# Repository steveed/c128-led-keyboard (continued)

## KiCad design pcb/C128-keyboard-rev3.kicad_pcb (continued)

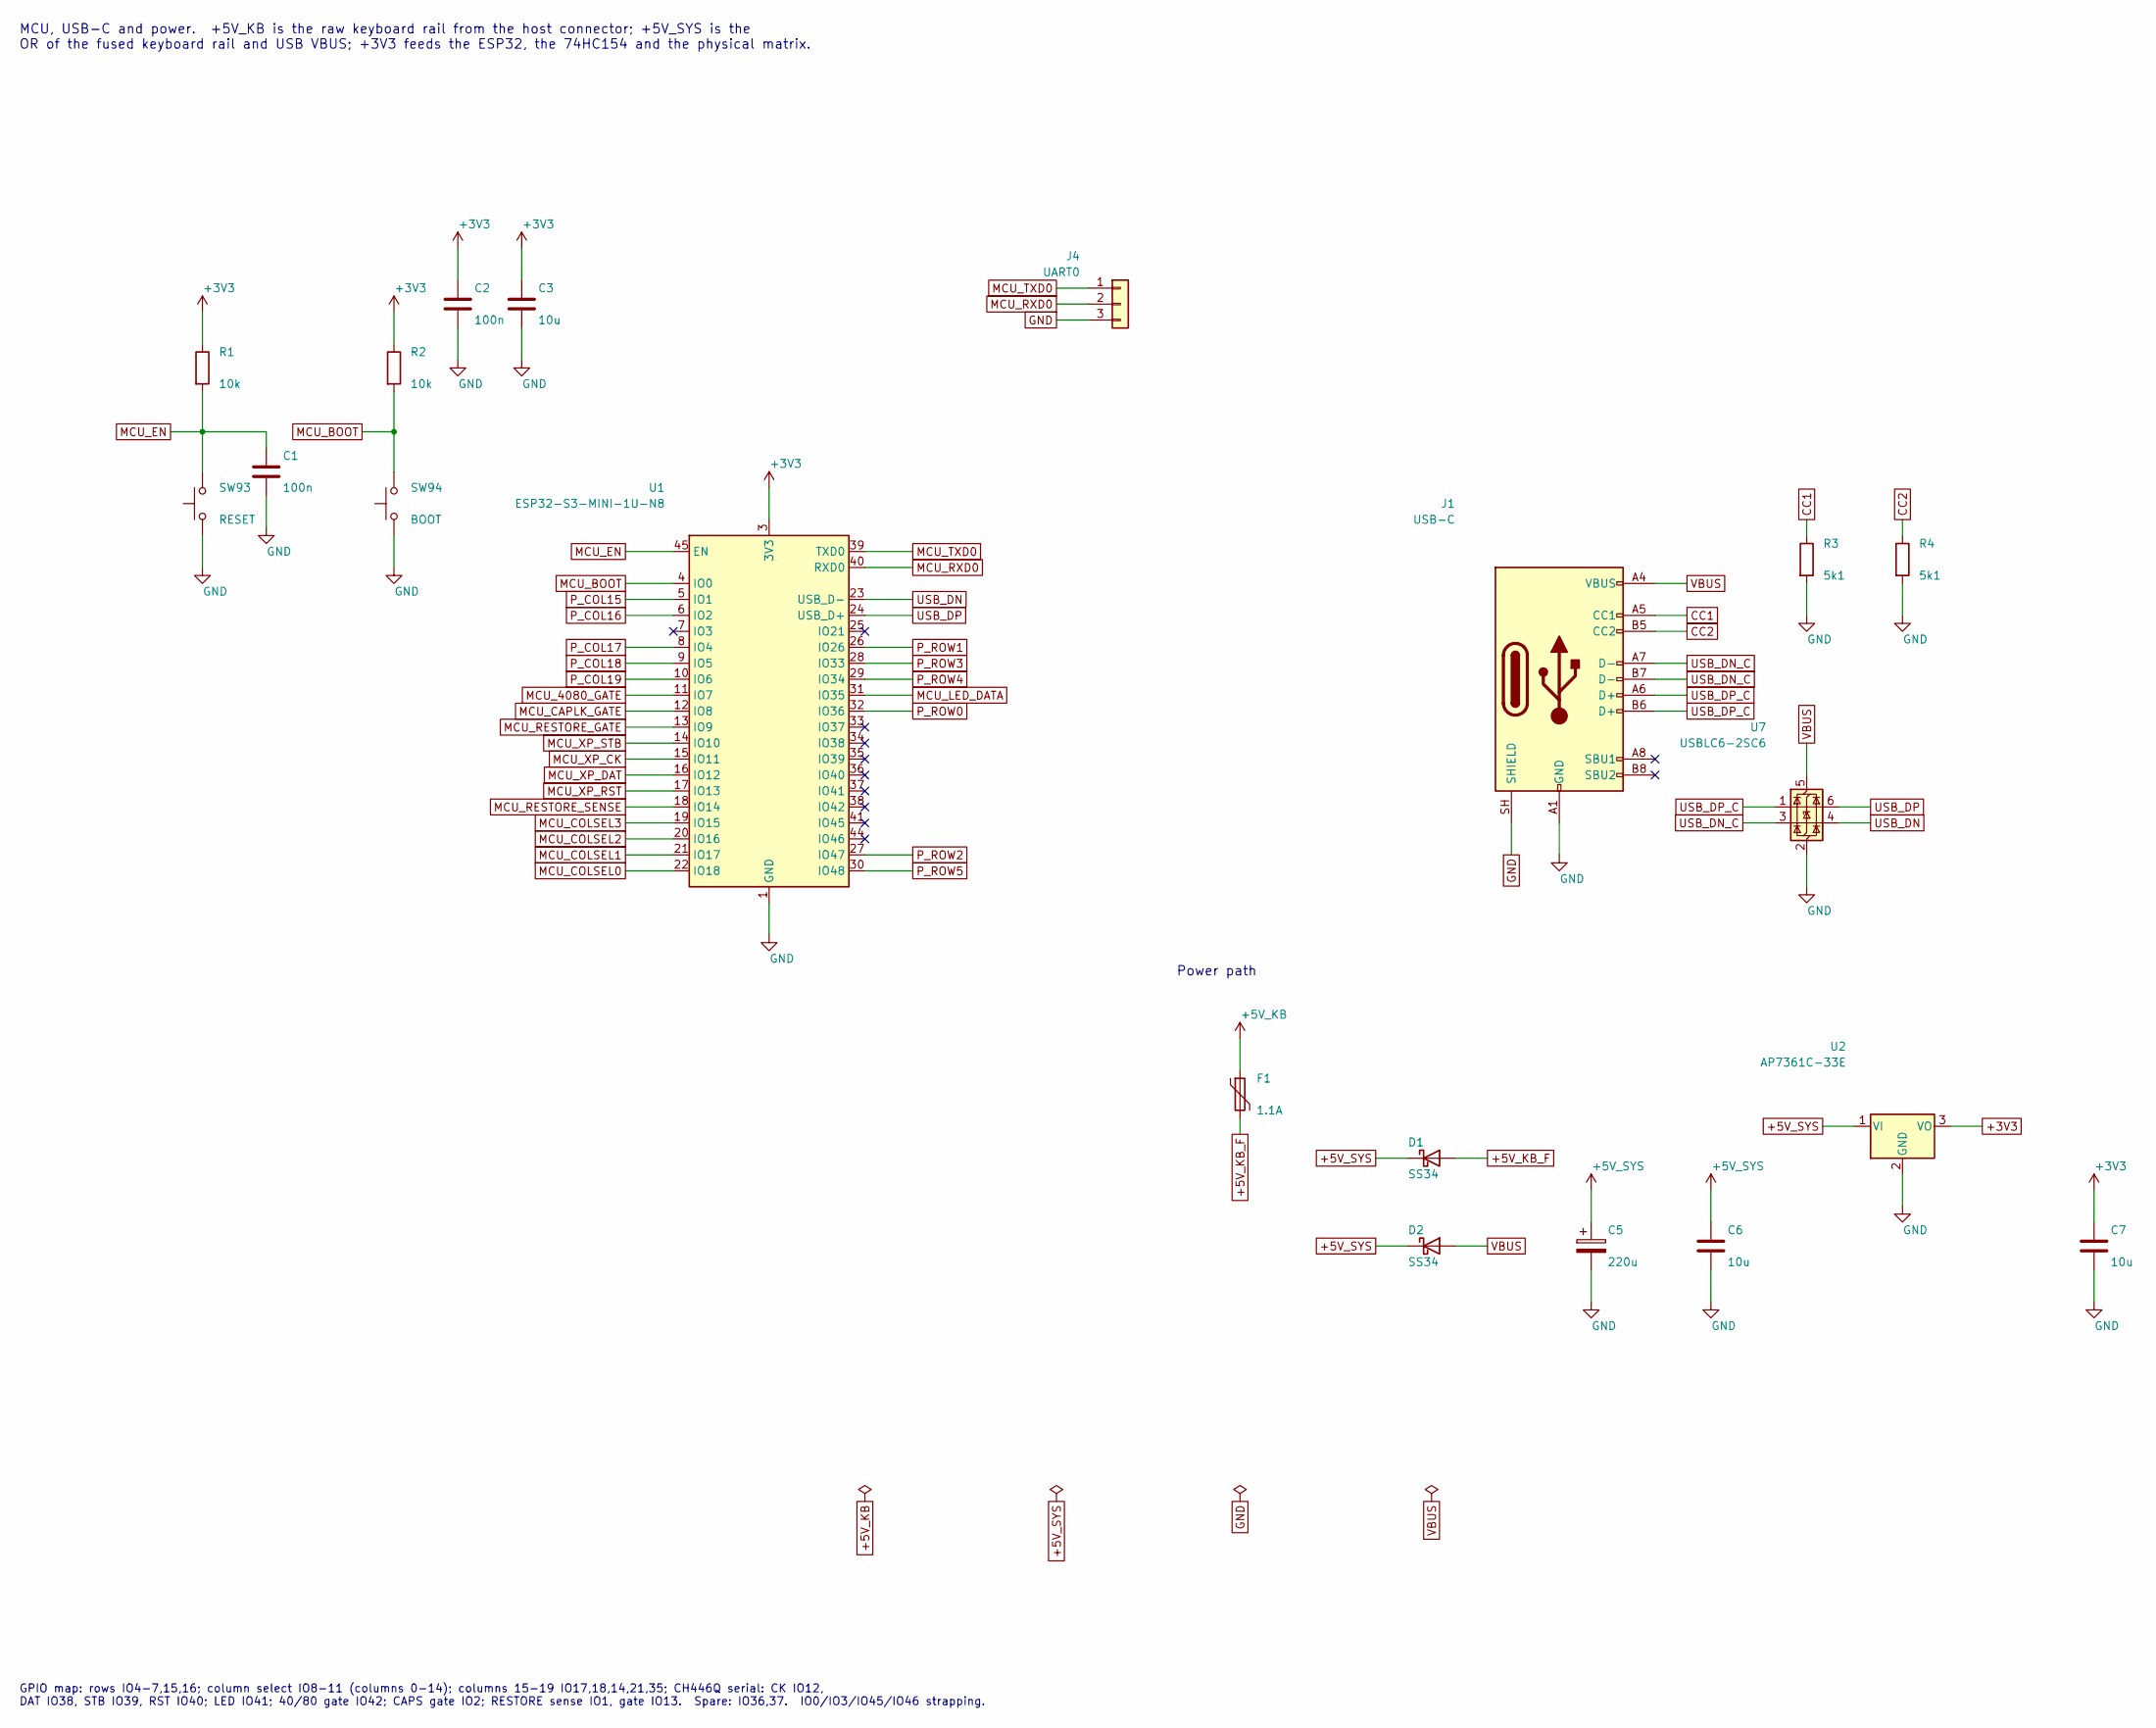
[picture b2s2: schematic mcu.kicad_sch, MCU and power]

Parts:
C1, C2: 100n; C_0603_1608Metric_Pad1.08x0.95mm_HandSolder; LCSC C14663
C3: 10u; C_0603_1608Metric_Pad1.08x0.95mm_HandSolder; LCSC C19702
C5: 220u; CP_Elec_6.3x7.7; LCSC C125979
C6, C7: 10u; C_1206_3216Metric_Pad1.33x1.80mm_HandSolder; LCSC C13585
D1, D2: SS34; D_SMA; LCSC C8678
F1: 1.1A; Fuse_1812_4532Metric; LCSC C142746
J1: USB-C; USB_C_Receptacle_ShouHan_TYPE-C-16P-3MD-040; LCSC C41417453
J4: UART0; PinHeader_1x03_P2.54mm_Vertical
R1, R2: 10k; R_0603_1608Metric_Pad0.98x0.95mm_HandSolder; LCSC C25804
R3, R4: 5k1; R_0603_1608Metric_Pad0.98x0.95mm_HandSolder; LCSC C23186
SW93: RESET; SW_SPST_PTS645Sx43SMTR92; LCSC C221880
SW94: BOOT; SW_SPST_PTS645Sx43SMTR92; LCSC C221880
U1: ESP32-S3-MINI-1U-N8; ESP32-S2-MINI-1U; LCSC C2980299
U2: AP7361C-33E; SOT-223-3_TabPin2; LCSC C500795
U7: USBLC6-2SC6; SOT-23-6; LCSC C7519

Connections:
+3V3: C2.1, C3.1, C7.1, R1.1, R2.1, U1.3 (3V3), U2.3 (VO); also elsewhere on the board
+5V_KB: F1.1; also elsewhere on the board
+5V_KB_F: D1.2 (A), F1.2
CC1: J1.A5 (CC1), R3.1
CC2: J1.B5 (CC2), R4.1
GND: C1.2, C2.2, C3.2, C5.2, C6.2, C7.2, J1.A1 (GND), J1.A12 (GND), J1.B1 (GND), J1.B12 (GND), J1.SH (SHIELD), J4.3, R3.2, R4.2, SW93.1, SW94.1, U1.1 (GND), U1.2 (GND), U1.42 (GND), U1.43 (GND), U1.46 (GND), U1.47 (GND), U1.48 (GND), U1.49 (GND), U1.50 (GND), U1.51 (GND), U1.52 (GND), U1.53 (GND), U1.54 (GND), U1.55 (GND), U1.56 (GND), U1.57 (GND), U1.58 (GND), U1.59 (GND), U1.60 (GND), U1.61 (GND), U1.62 (GND), U1.63 (GND), U1.64 (GND), U1.65 (GND), U2.2 (GND), U7.2 (GND); also elsewhere on the board
MCU_4080_GATE: U1.11 (IO7); also elsewhere on the board
MCU_BOOT: R2.2, SW94.2, U1.4 (IO0)
MCU_CAPLK_GATE: U1.12 (IO8); also elsewhere on the board
MCU_COLSEL0: U1.22 (IO18); also elsewhere on the board
MCU_COLSEL1: U1.21 (IO17); also elsewhere on the board
MCU_COLSEL2: U1.20 (IO16); also elsewhere on the board
MCU_COLSEL3: U1.19 (IO15); also elsewhere on the board
MCU_EN: C1.1, R1.2, SW93.2, U1.45 (EN)
MCU_LED_DATA: U1.31 (IO35); also elsewhere on the board
MCU_LED_EN: U1.34 (IO38); also elsewhere on the board
MCU_RESTORE_GATE: U1.13 (IO9); also elsewhere on the board
MCU_RESTORE_SENSE: U1.18 (IO14); also elsewhere on the board
MCU_RXD0: J4.2, U1.40 (RXD0)
MCU_TXD0: J4.1, U1.39 (TXD0)
MCU_XP_CK: U1.15 (IO11); also elsewhere on the board
MCU_XP_DAT: U1.16 (IO12); also elsewhere on the board
MCU_XP_RST: U1.17 (IO13); also elsewhere on the board
MCU_XP_STB: U1.14 (IO10); also elsewhere on the board
P_COL15: U1.5 (IO1); also elsewhere on the board
P_COL16: U1.6 (IO2); also elsewhere on the board
P_COL17: U1.8 (IO4); also elsewhere on the board
P_COL18: U1.9 (IO5); also elsewhere on the board
P_COL19: U1.10 (IO6); also elsewhere on the board
P_ROW0: U1.32 (IO36); also elsewhere on the board
P_ROW1: U1.26 (IO26); also elsewhere on the board
P_ROW2: U1.27 (IO47); also elsewhere on the board
P_ROW3: U1.28 (IO33); also elsewhere on the board
P_ROW4: U1.29 (IO34); also elsewhere on the board
P_ROW5: U1.30 (IO48); also elsewhere on the board
USB_DN: U1.23 (USB_D-), U7.4 (I/O2)
USB_DN_C: J1.A7 (D-), J1.B7 (D-), U7.3 (I/O2)
USB_DP: U1.24 (USB_D+), U7.6 (I/O1)
USB_DP_C: J1.A6 (D+), J1.B6 (D+), U7.1 (I/O1)
VBUS: D2.2 (A), J1.A4 (VBUS), J1.A9 (VBUS), J1.B4 (VBUS), J1.B9 (VBUS), U7.5 (VBUS)

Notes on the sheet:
GPIO map: rows IO4-7,15,16; column select IO8-11 (columns 0-14); columns 15-19 IO17,18,14,21,35; CH446Q serial: CK IO12, DAT IO38, STB IO39, RST IO40; LED IO41; 40/80 gate IO42; CAPS gate IO2; RESTORE sense IO1, gate IO13. Spare: IO36,37. IO0/IO3/IO45/IO46 strapping.
MCU, USB-C and power. +5V_KB is the raw keyboard rail from the host connector; +5V_SYS is the OR of the fused keyboard rail and USB VBUS; +3V3 feeds the ESP32, the 74HC154 and the physical matrix.
Power path

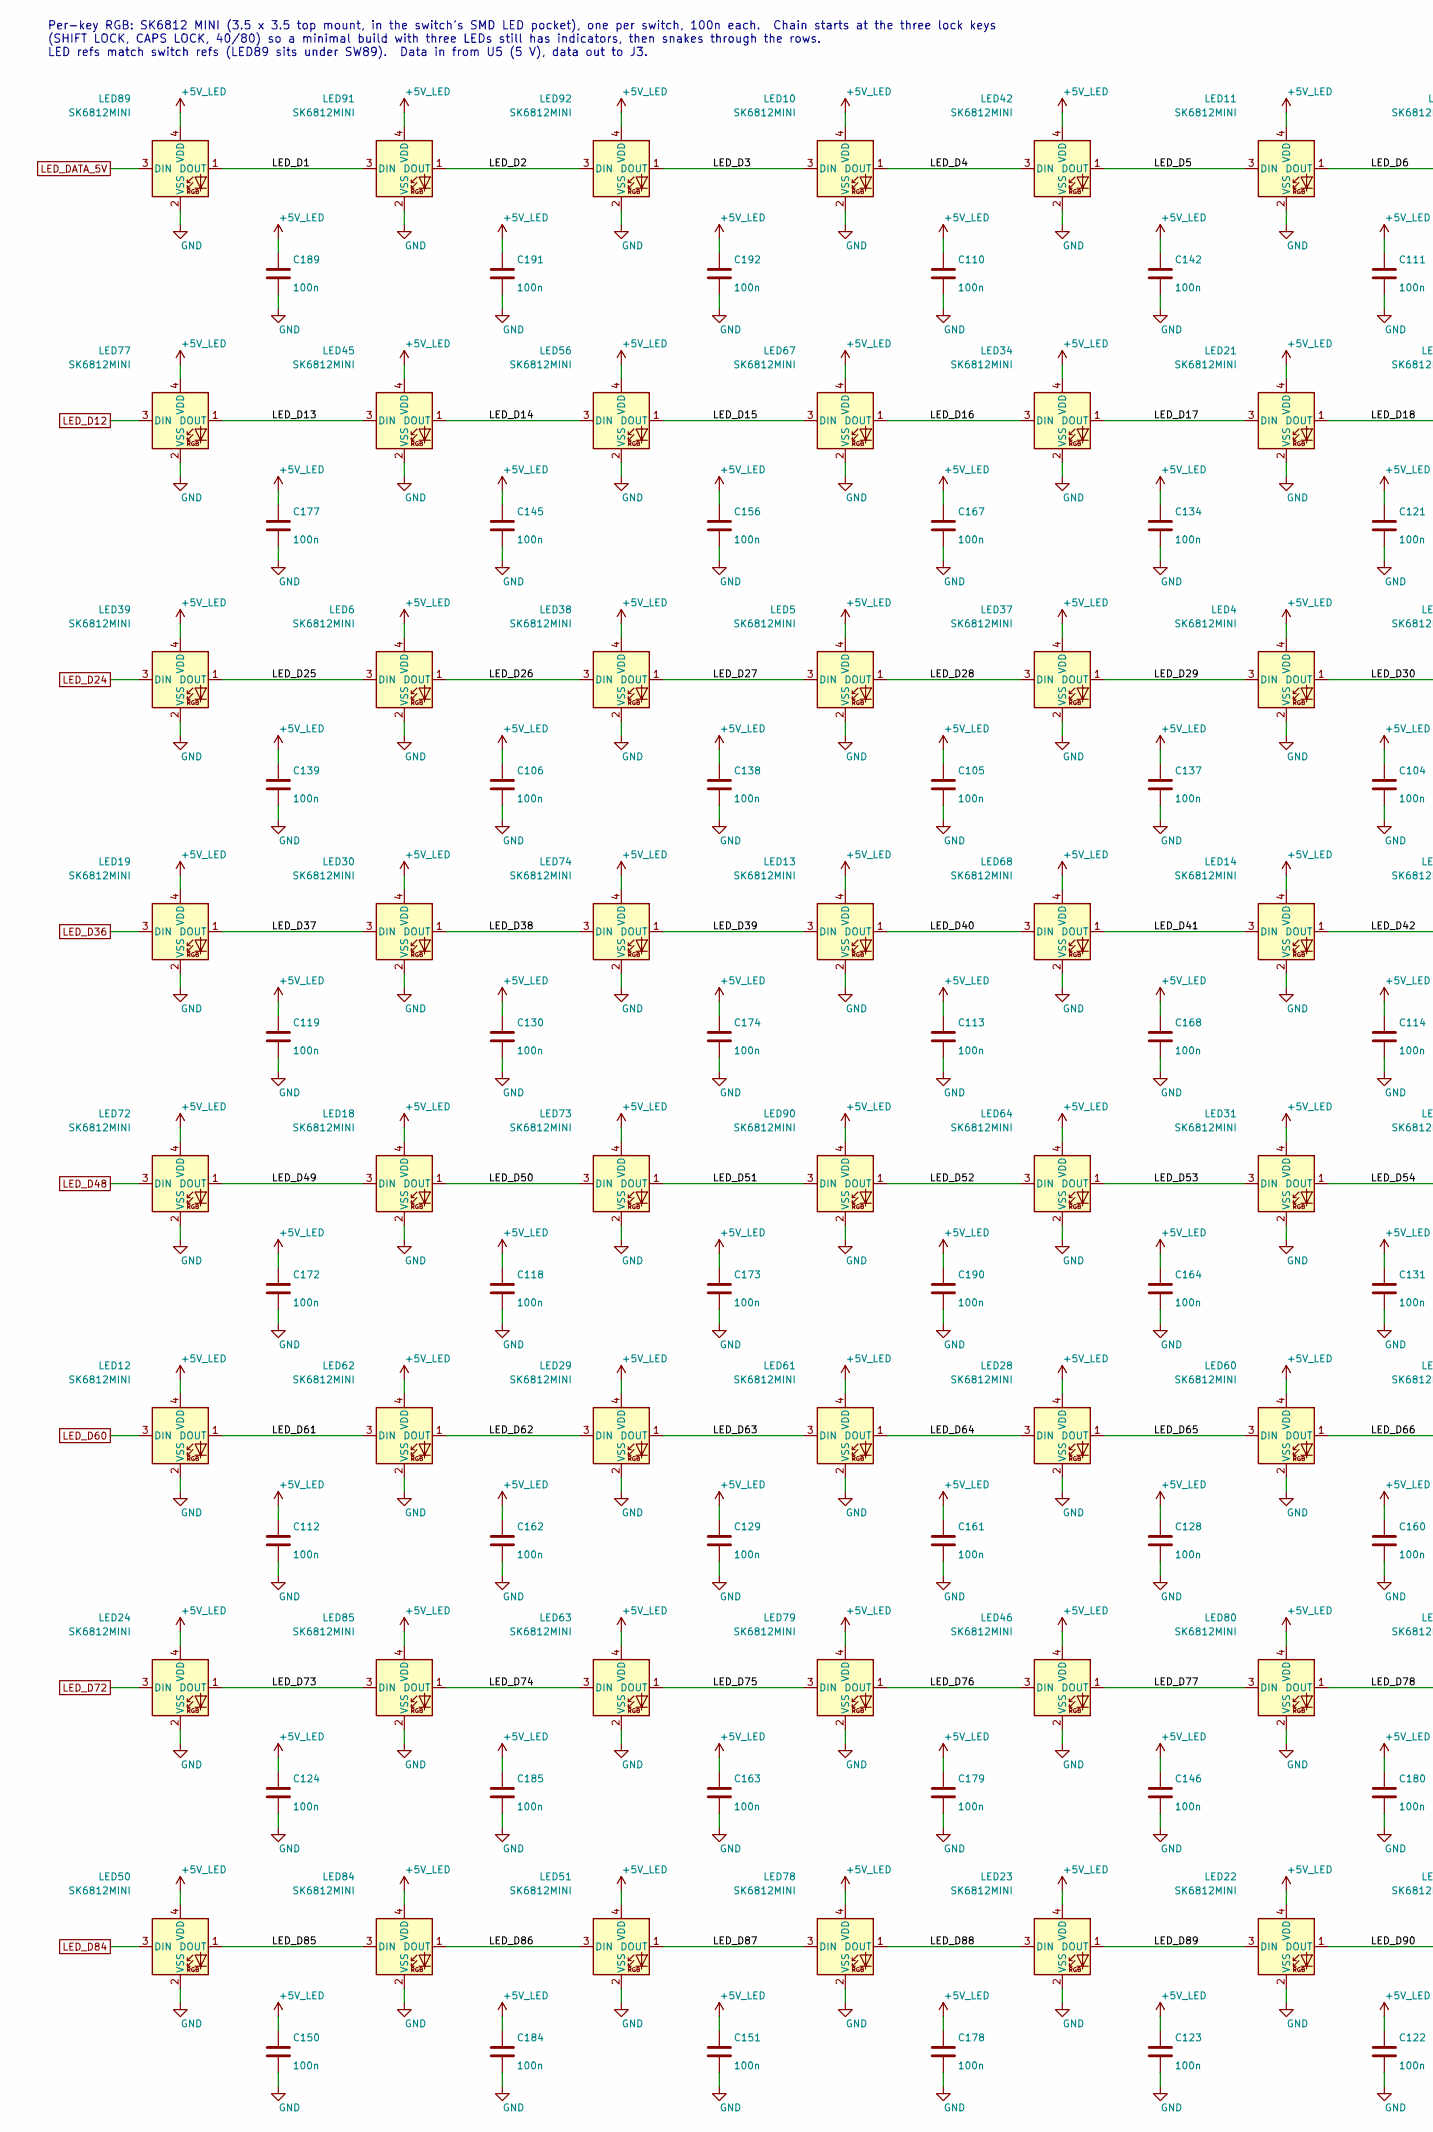
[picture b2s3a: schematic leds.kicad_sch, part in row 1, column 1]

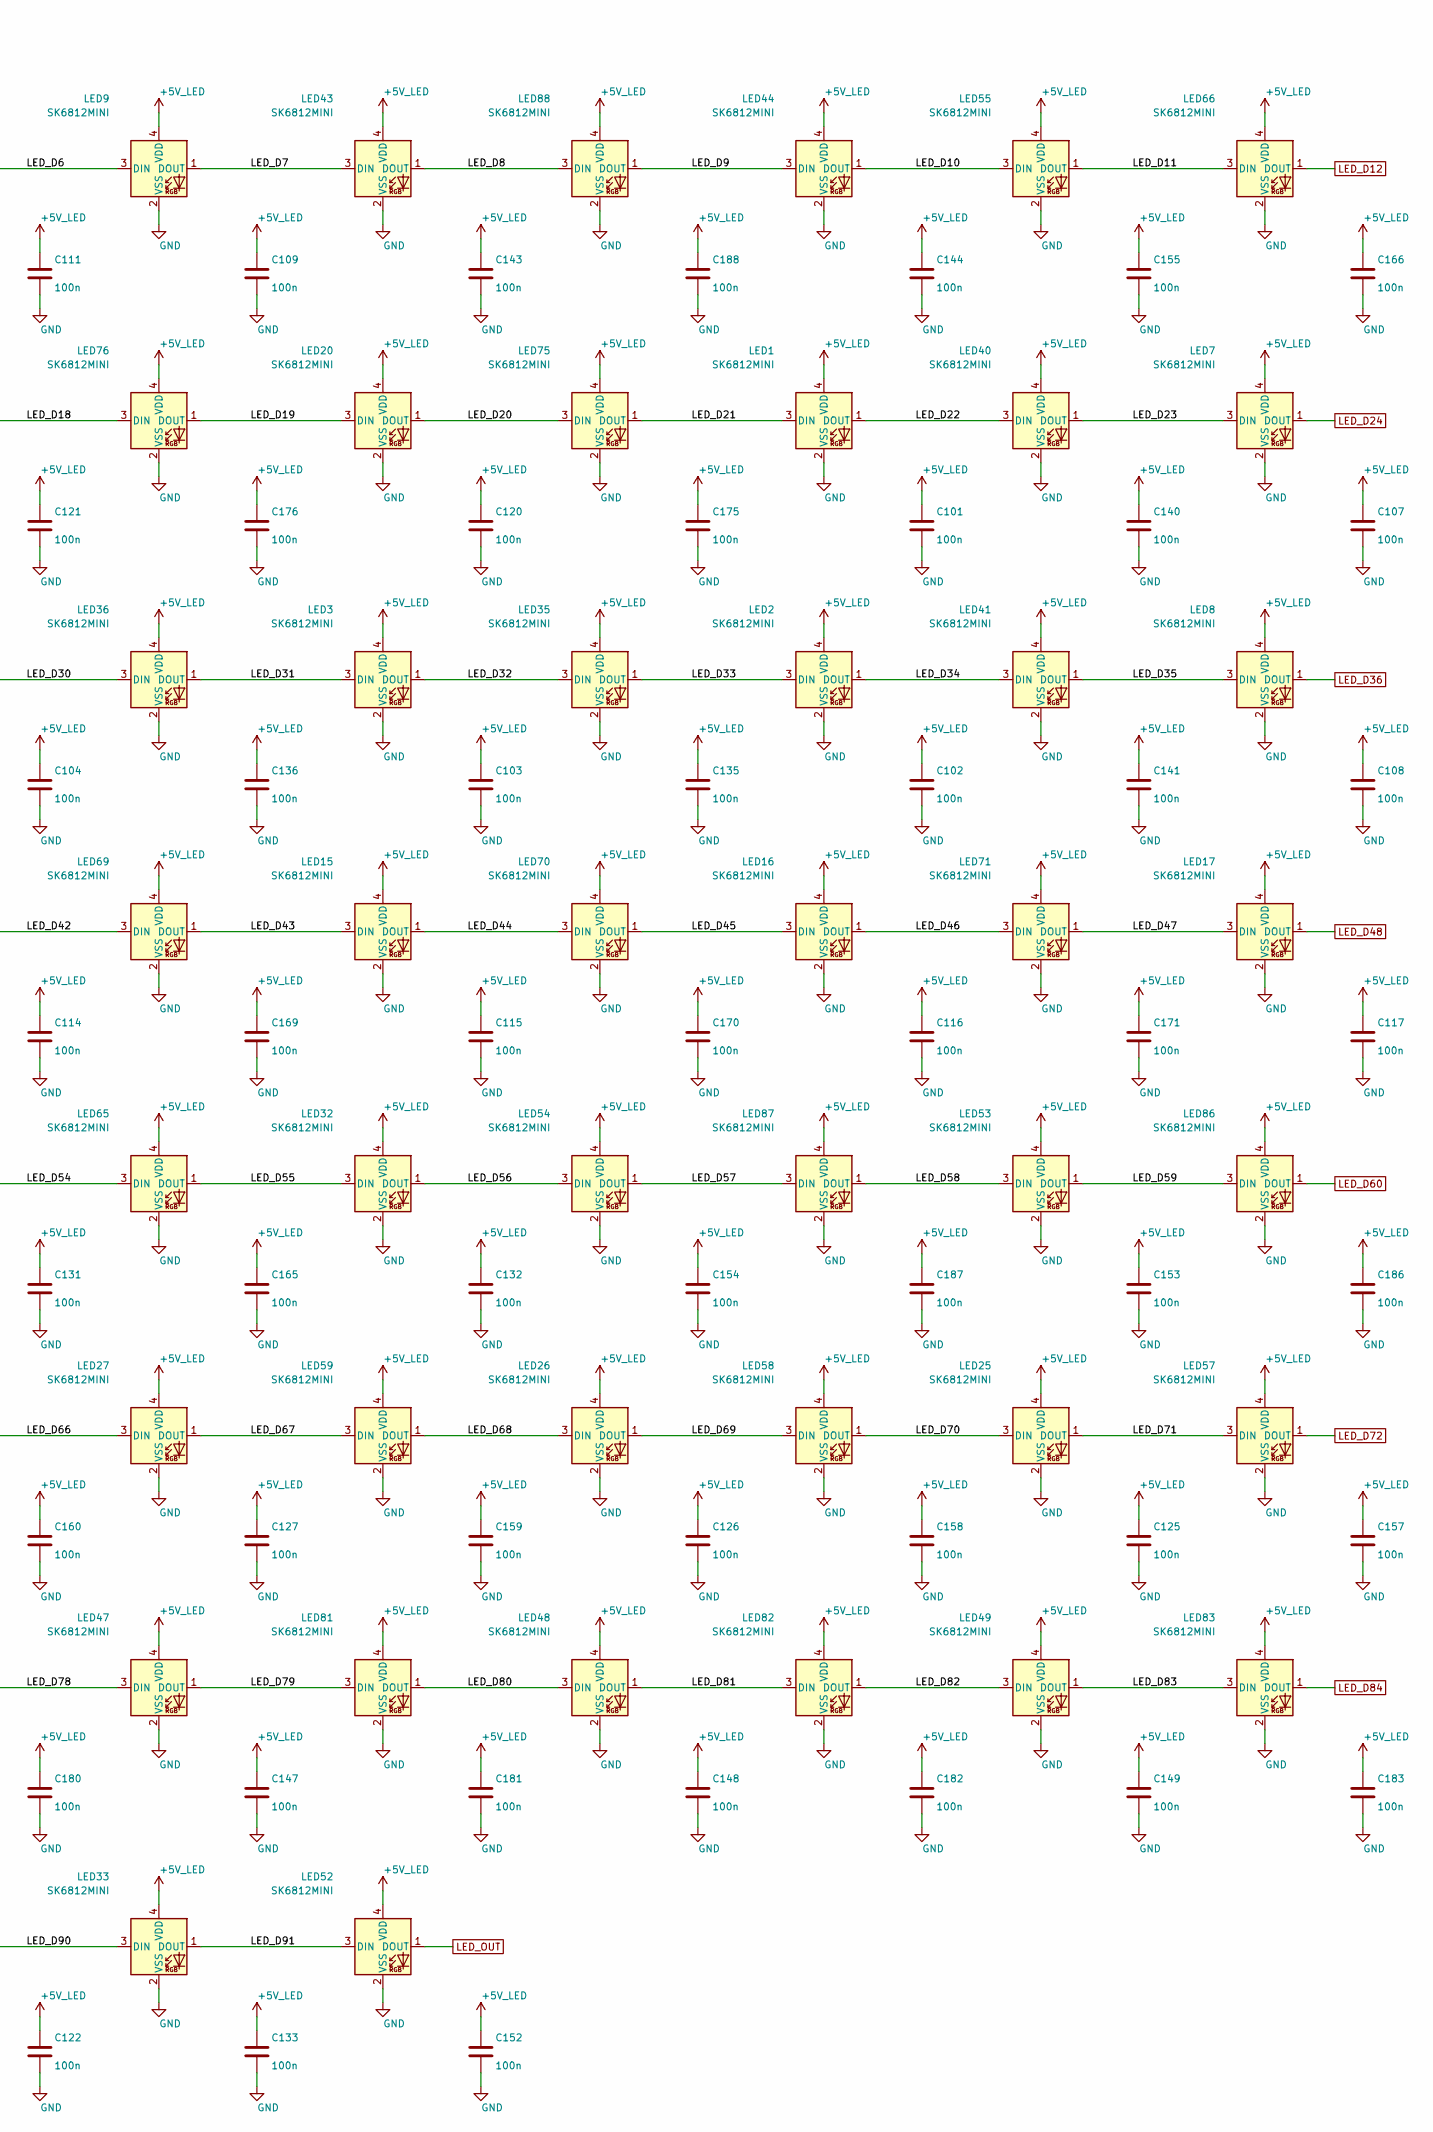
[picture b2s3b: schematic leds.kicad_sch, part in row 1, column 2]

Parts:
C101, C102, C103, C104, C105, C106, C107, C108, C109, C110, C111, C112, C113, C114, C115, C116, C117, C118, C119, C120, C121, C122, C123, C124, C125, C126, C127, C128, C129, C130, C131, C132, C133, C134, C135, C136, C137, C138, C139, C140, C141, C142, C143, C144, C145, C146, C147, C148, C149, C150, C151, C152, C153, C154, C155, C156, C157, C158, C159, C160, C161, C162, C163, C164, C165, C166, C167, C168, C169, C170, C171, C172, C173, C174, C175, C176, C177, C178, C179, C180, C181, C182, C183, C184, C185, C186, C187, C188, C189, C190, C191, C192: 100n; C_0603_1608Metric_Pad1.08x0.95mm_HandSolder; LCSC C14663
LED1, LED2, LED3, LED4, LED5, LED6, LED7, LED8, LED9, LED10, LED11, LED12, LED13, LED14, LED15, LED16, LED17, LED18, LED19, LED20, LED21, LED22, LED23, LED24, LED25, LED26, LED27, LED28, LED29, LED30, LED31, LED32, LED33, LED34, LED35, LED36, LED37, LED38, LED39, LED40, LED41, LED42, LED43, LED44, LED45, LED46, LED47, LED48, LED49, LED50, LED51, LED52, LED53, LED54, LED55, LED56, LED57, LED58, LED59, LED60, LED61, LED62, LED63, LED64, LED65, LED66, LED67, LED68, LED69, LED70, LED71, LED72, LED73, LED74, LED75, LED76, LED77, LED78, LED79, LED80, LED81, LED82, LED83, LED84, LED85, LED86, LED87, LED88, LED89, LED90, LED91, LED92: SK6812MINI; LED_SK6812MINI_MX; LCSC C2886570

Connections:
/LEDs/LED_D1: LED89.1 (DOUT), LED91.3 (DIN)
/LEDs/LED_D2: LED91.1 (DOUT), LED92.3 (DIN)
/LEDs/LED_D3: LED10.3 (DIN), LED92.1 (DOUT)
/LEDs/LED_D4: LED10.1 (DOUT), LED42.3 (DIN)
/LEDs/LED_D5: LED11.3 (DIN), LED42.1 (DOUT)
/LEDs/LED_D6: LED9.3 (DIN), LED11.1 (DOUT)
/LEDs/LED_D7: LED9.1 (DOUT), LED43.3 (DIN)
/LEDs/LED_D8: LED43.1 (DOUT), LED88.3 (DIN)
/LEDs/LED_D9: LED44.3 (DIN), LED88.1 (DOUT)
/LEDs/LED_D10: LED44.1 (DOUT), LED55.3 (DIN)
/LEDs/LED_D11: LED55.1 (DOUT), LED66.3 (DIN)
/LEDs/LED_D13: LED45.3 (DIN), LED77.1 (DOUT)
/LEDs/LED_D14: LED45.1 (DOUT), LED56.3 (DIN)
/LEDs/LED_D15: LED56.1 (DOUT), LED67.3 (DIN)
/LEDs/LED_D16: LED34.3 (DIN), LED67.1 (DOUT)
/LEDs/LED_D17: LED21.3 (DIN), LED34.1 (DOUT)
/LEDs/LED_D18: LED21.1 (DOUT), LED76.3 (DIN)
/LEDs/LED_D19: LED20.3 (DIN), LED76.1 (DOUT)
/LEDs/LED_D20: LED20.1 (DOUT), LED75.3 (DIN)
/LEDs/LED_D21: LED1.3 (DIN), LED75.1 (DOUT)
/LEDs/LED_D22: LED1.1 (DOUT), LED40.3 (DIN)
/LEDs/LED_D23: LED7.3 (DIN), LED40.1 (DOUT)
/LEDs/LED_D25: LED6.3 (DIN), LED39.1 (DOUT)
/LEDs/LED_D26: LED6.1 (DOUT), LED38.3 (DIN)
/LEDs/LED_D27: LED5.3 (DIN), LED38.1 (DOUT)
/LEDs/LED_D28: LED5.1 (DOUT), LED37.3 (DIN)
/LEDs/LED_D29: LED4.3 (DIN), LED37.1 (DOUT)
/LEDs/LED_D30: LED4.1 (DOUT), LED36.3 (DIN)
/LEDs/LED_D31: LED3.3 (DIN), LED36.1 (DOUT)
/LEDs/LED_D32: LED3.1 (DOUT), LED35.3 (DIN)
/LEDs/LED_D33: LED2.3 (DIN), LED35.1 (DOUT)
/LEDs/LED_D34: LED2.1 (DOUT), LED41.3 (DIN)
/LEDs/LED_D35: LED8.3 (DIN), LED41.1 (DOUT)
/LEDs/LED_D37: LED19.1 (DOUT), LED30.3 (DIN)
/LEDs/LED_D38: LED30.1 (DOUT), LED74.3 (DIN)
/LEDs/LED_D39: LED13.3 (DIN), LED74.1 (DOUT)
/LEDs/LED_D40: LED13.1 (DOUT), LED68.3 (DIN)
/LEDs/LED_D41: LED14.3 (DIN), LED68.1 (DOUT)
/LEDs/LED_D42: LED14.1 (DOUT), LED69.3 (DIN)
/LEDs/LED_D43: LED15.3 (DIN), LED69.1 (DOUT)
/LEDs/LED_D44: LED15.1 (DOUT), LED70.3 (DIN)
/LEDs/LED_D45: LED16.3 (DIN), LED70.1 (DOUT)
/LEDs/LED_D46: LED16.1 (DOUT), LED71.3 (DIN)
/LEDs/LED_D47: LED17.3 (DIN), LED71.1 (DOUT)
/LEDs/LED_D49: LED18.3 (DIN), LED72.1 (DOUT)
/LEDs/LED_D50: LED18.1 (DOUT), LED73.3 (DIN)
/LEDs/LED_D51: LED73.1 (DOUT), LED90.3 (DIN)
/LEDs/LED_D52: LED64.3 (DIN), LED90.1 (DOUT)
/LEDs/LED_D53: LED31.3 (DIN), LED64.1 (DOUT)
/LEDs/LED_D54: LED31.1 (DOUT), LED65.3 (DIN)
/LEDs/LED_D55: LED32.3 (DIN), LED65.1 (DOUT)
/LEDs/LED_D56: LED32.1 (DOUT), LED54.3 (DIN)
/LEDs/LED_D57: LED54.1 (DOUT), LED87.3 (DIN)
/LEDs/LED_D58: LED53.3 (DIN), LED87.1 (DOUT)
/LEDs/LED_D59: LED53.1 (DOUT), LED86.3 (DIN)
/LEDs/LED_D61: LED12.1 (DOUT), LED62.3 (DIN)
/LEDs/LED_D62: LED29.3 (DIN), LED62.1 (DOUT)
/LEDs/LED_D63: LED29.1 (DOUT), LED61.3 (DIN)
/LEDs/LED_D64: LED28.3 (DIN), LED61.1 (DOUT)
/LEDs/LED_D65: LED28.1 (DOUT), LED60.3 (DIN)
/LEDs/LED_D66: LED27.3 (DIN), LED60.1 (DOUT)
/LEDs/LED_D67: LED27.1 (DOUT), LED59.3 (DIN)
/LEDs/LED_D68: LED26.3 (DIN), LED59.1 (DOUT)
/LEDs/LED_D69: LED26.1 (DOUT), LED58.3 (DIN)
/LEDs/LED_D70: LED25.3 (DIN), LED58.1 (DOUT)
/LEDs/LED_D71: LED25.1 (DOUT), LED57.3 (DIN)
/LEDs/LED_D73: LED24.1 (DOUT), LED85.3 (DIN)
/LEDs/LED_D74: LED63.3 (DIN), LED85.1 (DOUT)
/LEDs/LED_D75: LED63.1 (DOUT), LED79.3 (DIN)
/LEDs/LED_D76: LED46.3 (DIN), LED79.1 (DOUT)
/LEDs/LED_D77: LED46.1 (DOUT), LED80.3 (DIN)
/LEDs/LED_D78: LED47.3 (DIN), LED80.1 (DOUT)
/LEDs/LED_D79: LED47.1 (DOUT), LED81.3 (DIN)
/LEDs/LED_D80: LED48.3 (DIN), LED81.1 (DOUT)
/LEDs/LED_D81: LED48.1 (DOUT), LED82.3 (DIN)
/LEDs/LED_D82: LED49.3 (DIN), LED82.1 (DOUT)
/LEDs/LED_D83: LED49.1 (DOUT), LED83.3 (DIN)
/LEDs/LED_D85: LED50.1 (DOUT), LED84.3 (DIN)
/LEDs/LED_D86: LED51.3 (DIN), LED84.1 (DOUT)
/LEDs/LED_D87: LED51.1 (DOUT), LED78.3 (DIN)
/LEDs/LED_D88: LED23.3 (DIN), LED78.1 (DOUT)
/LEDs/LED_D89: LED22.3 (DIN), LED23.1 (DOUT)
/LEDs/LED_D90: LED22.1 (DOUT), LED33.3 (DIN)
/LEDs/LED_D91: LED33.1 (DOUT), LED52.3 (DIN)
GND: C101.2, C102.2, C103.2, C104.2, C105.2, C106.2, C107.2, C108.2, C109.2, C110.2, C111.2, C112.2, C113.2, C114.2, C115.2, C116.2, C117.2, C118.2, C119.2, C120.2, C121.2, C122.2, C123.2, C124.2, C125.2, C126.2, C127.2, C128.2, C129.2, C130.2, C131.2, C132.2, C133.2, C134.2, C135.2, C136.2, C137.2, C138.2, C139.2, C140.2, C141.2, C142.2, C143.2, C144.2, C145.2, C146.2, C147.2, C148.2, C149.2, C150.2, C151.2, C152.2, C153.2, C154.2, C155.2, C156.2, C157.2, C158.2, C159.2, C160.2, C161.2, C162.2, C163.2, C164.2, C165.2, C166.2, C167.2, C168.2, C169.2, C170.2, C171.2, C172.2, C173.2, C174.2, C175.2, C176.2, C177.2, C178.2, C179.2, C180.2, C181.2, C182.2, C183.2, C184.2, C185.2, C186.2, C187.2, C188.2, C189.2, C190.2, C191.2, C192.2, LED1.2 (VSS), LED2.2 (VSS), LED3.2 (VSS), LED4.2 (VSS), LED5.2 (VSS), LED6.2 (VSS), LED7.2 (VSS), LED8.2 (VSS), LED9.2 (VSS), LED10.2 (VSS), LED11.2 (VSS), LED12.2 (VSS), LED13.2 (VSS), LED14.2 (VSS), LED15.2 (VSS), LED16.2 (VSS), LED17.2 (VSS), LED18.2 (VSS), LED19.2 (VSS), LED20.2 (VSS), LED21.2 (VSS), LED22.2 (VSS), LED23.2 (VSS), LED24.2 (VSS), LED25.2 (VSS), LED26.2 (VSS), LED27.2 (VSS), LED28.2 (VSS), LED29.2 (VSS), LED30.2 (VSS), LED31.2 (VSS), LED32.2 (VSS), LED33.2 (VSS), LED34.2 (VSS), LED35.2 (VSS), LED36.2 (VSS), LED37.2 (VSS), LED38.2 (VSS), LED39.2 (VSS), LED40.2 (VSS), LED41.2 (VSS), LED42.2 (VSS), LED43.2 (VSS), LED44.2 (VSS), LED45.2 (VSS), LED46.2 (VSS), LED47.2 (VSS), LED48.2 (VSS), LED49.2 (VSS), LED50.2 (VSS), LED51.2 (VSS), LED52.2 (VSS), LED53.2 (VSS), LED54.2 (VSS), LED55.2 (VSS), LED56.2 (VSS), LED57.2 (VSS), LED58.2 (VSS), LED59.2 (VSS), LED60.2 (VSS), LED61.2 (VSS), LED62.2 (VSS), LED63.2 (VSS), LED64.2 (VSS), LED65.2 (VSS), LED66.2 (VSS), LED67.2 (VSS), LED68.2 (VSS), LED69.2 (VSS), LED70.2 (VSS), LED71.2 (VSS), LED72.2 (VSS), LED73.2 (VSS), LED74.2 (VSS), LED75.2 (VSS), LED76.2 (VSS), LED77.2 (VSS), LED78.2 (VSS), LED79.2 (VSS), LED80.2 (VSS), LED81.2 (VSS), LED82.2 (VSS), LED83.2 (VSS), LED84.2 (VSS), LED85.2 (VSS), LED86.2 (VSS), LED87.2 (VSS), LED88.2 (VSS), LED89.2 (VSS), LED90.2 (VSS), LED91.2 (VSS), LED92.2 (VSS); also elsewhere on the board
LED_D12: LED66.1 (DOUT), LED77.3 (DIN)
LED_D24: LED7.1 (DOUT), LED39.3 (DIN)
LED_D36: LED8.1 (DOUT), LED19.3 (DIN)
LED_D48: LED17.1 (DOUT), LED72.3 (DIN)
LED_D60: LED12.3 (DIN), LED86.1 (DOUT)
LED_D72: LED24.3 (DIN), LED57.1 (DOUT)
LED_D84: LED50.3 (DIN), LED83.1 (DOUT)
LED_DATA_5V: LED89.3 (DIN); also elsewhere on the board
LED_OUT: LED52.1 (DOUT); also elsewhere on the board

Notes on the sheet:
Per-key RGB: SK6812 MINI (3.5 x 3.5 top mount, in the switch's SMD LED pocket), one per switch, 100n each. Chain starts at the three lock keys (SHIFT LOCK, CAPS LOCK, 40/80) so a minimal build with three LEDs still has indicators, then snakes through the rows. LED refs match switch refs (LED89 sits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

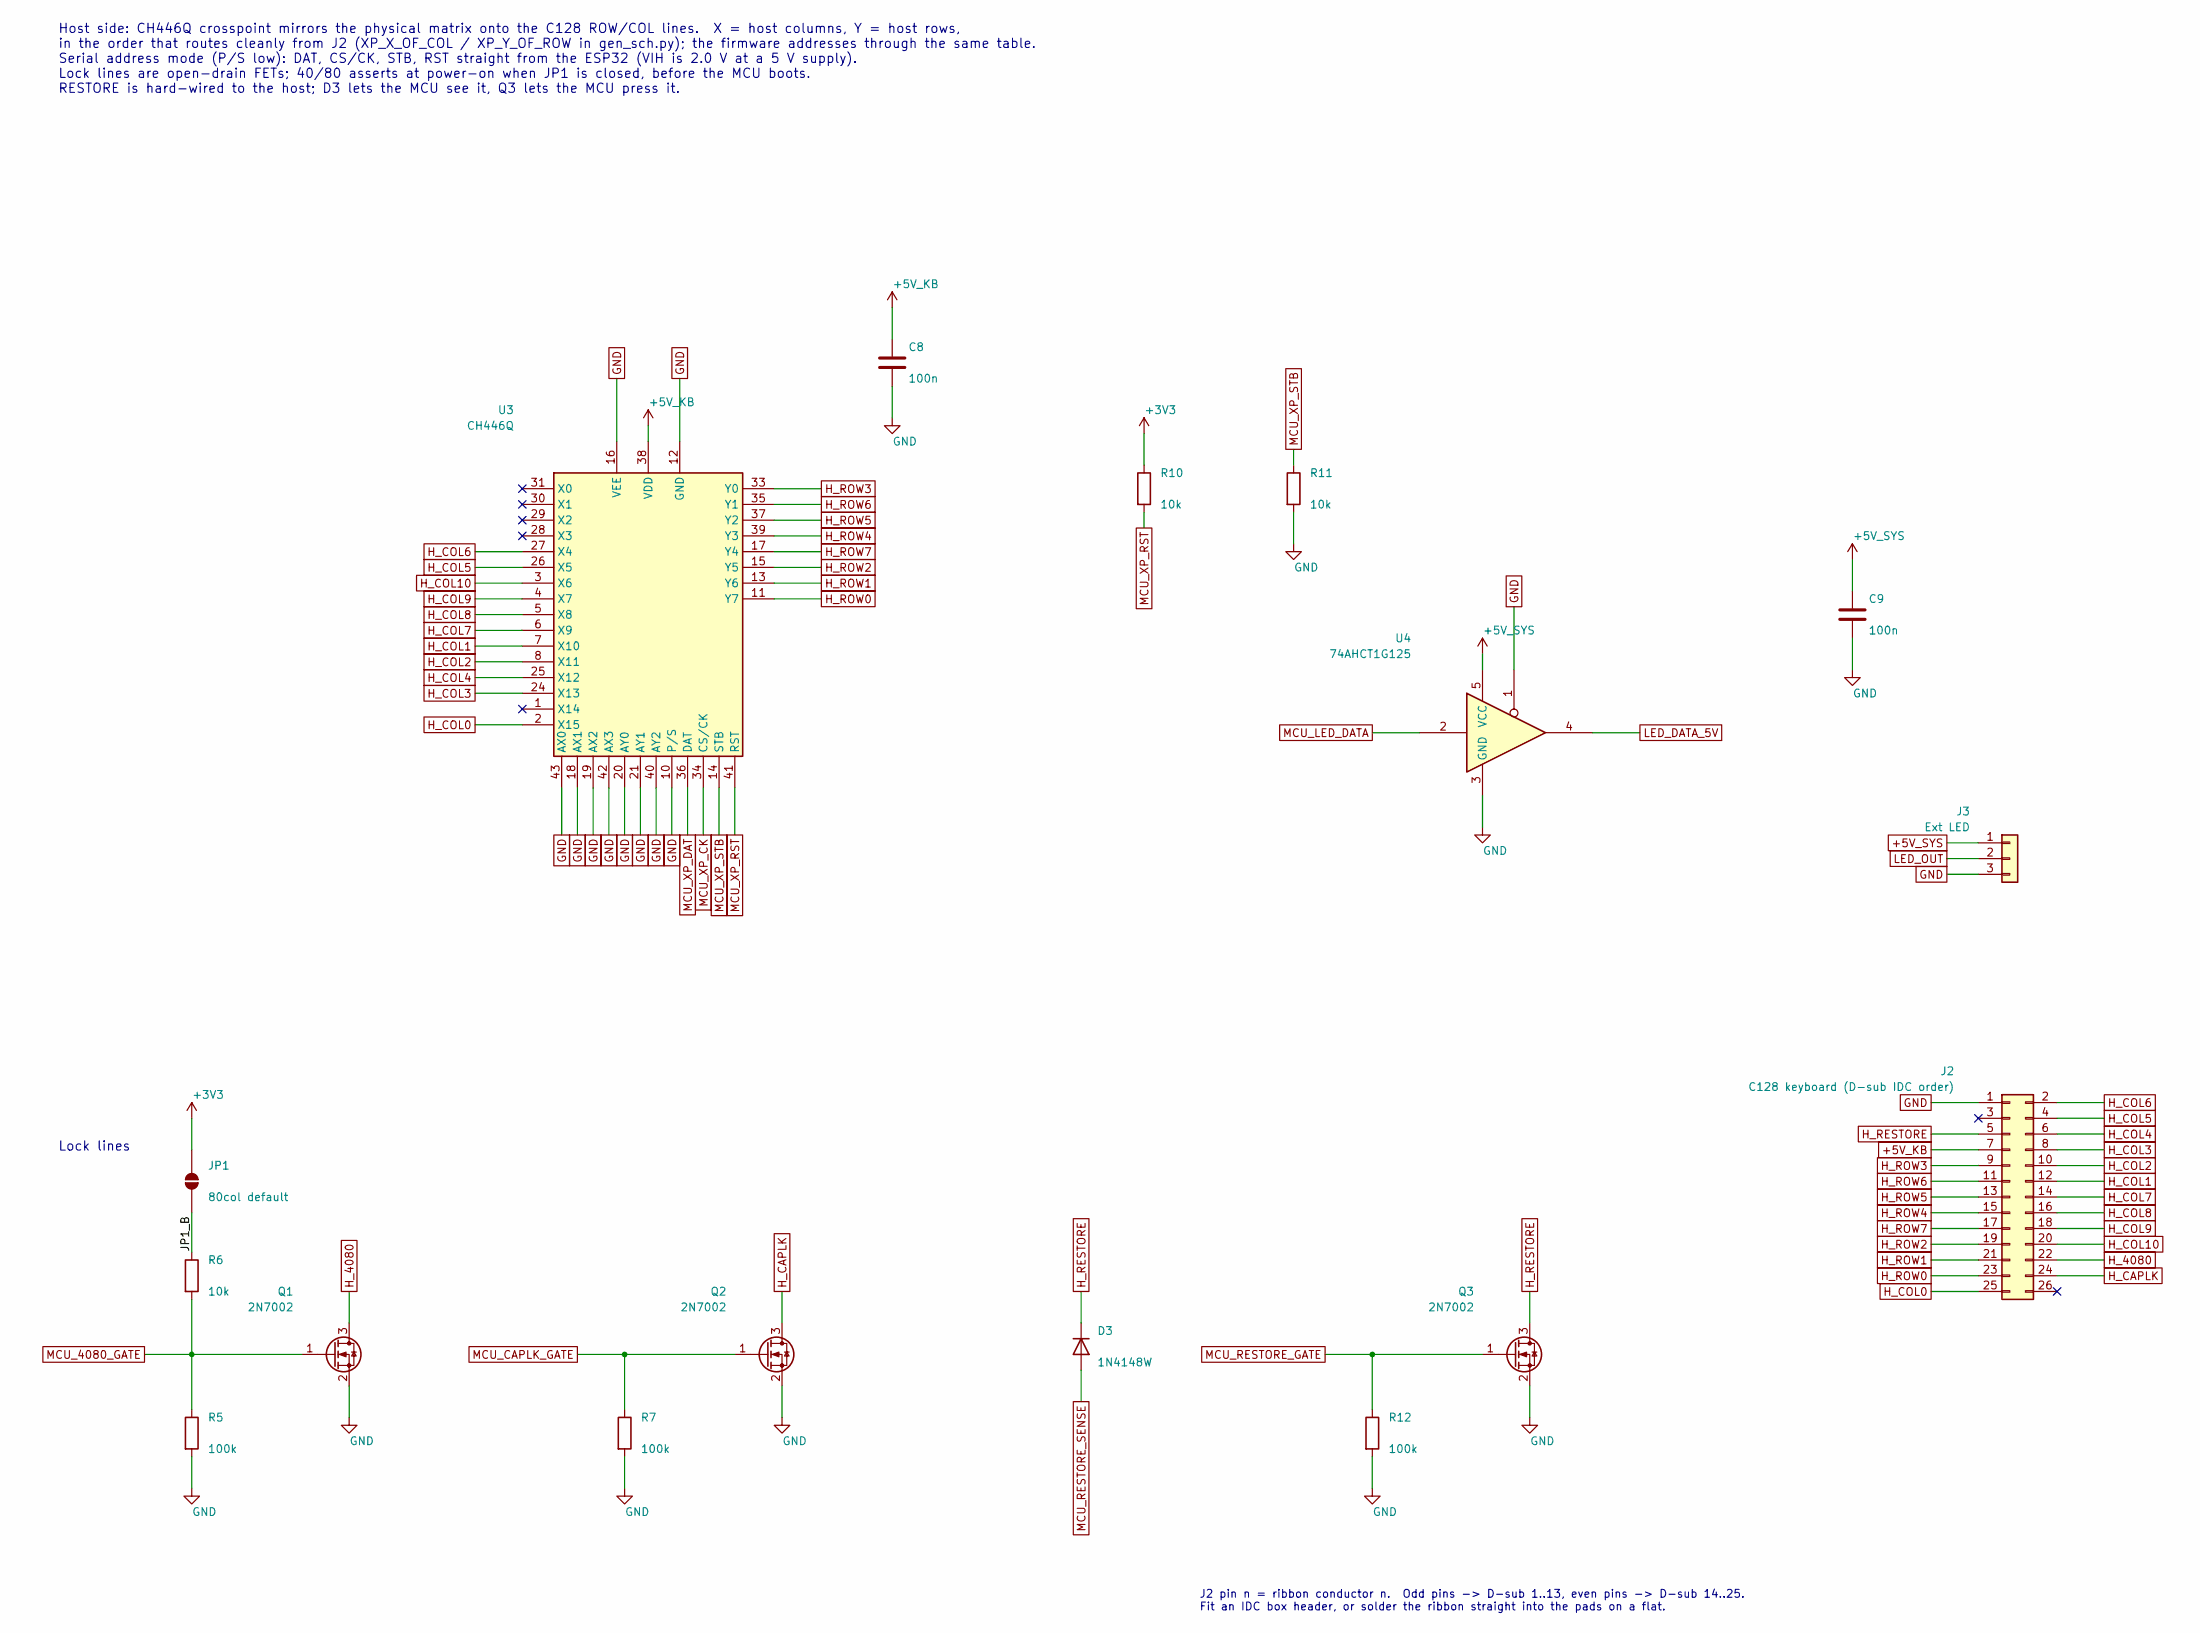
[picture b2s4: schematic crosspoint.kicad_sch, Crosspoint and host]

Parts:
C8, C9: 100n; C_0603_1608Metric_Pad1.08x0.95mm_HandSolder; LCSC C14663
D3: 1N4148W; D_SOD-123; LCSC C81598
J2: C128 keyboard (D-sub IDC order); IDC-Header_2x13_P2.54mm_Vertical
J3: Ext LED; PinHeader_1x03_P2.54mm_Vertical
JP1: 80col default; SolderJumper-2_P1.3mm_Open_RoundedPad1.0x1.5mm
Q1, Q2, Q3: 2N7002; SOT-23; LCSC C8545
R5, R7, R12: 100k; R_0603_1608Metric_Pad0.98x0.95mm_HandSolder; LCSC C25803
R6, R10, R11: 10k; R_0603_1608Metric_Pad0.98x0.95mm_HandSolder; LCSC C25804
U3: CH446Q; LQFP-44_10x10mm_P0.8mm; LCSC C109471
U4: 74AHCT1G125; SOT-23-5; LCSC C7484

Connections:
+3V3: JP1.2 (B), R10.1; also elsewhere on the board
+5V_KB: C8.1, J2.7, U3.38 (VDD); also elsewhere on the board
/Crosspoint and host/JP1_B: JP1.1 (A), R6.1
GND: C8.2, C9.2, J2.1, J3.3, Q1.2 (S), Q2.2 (S), Q3.2 (S), R5.2, R7.2, R11.2, R12.2, U3.10 (P/S), U3.12 (GND), U3.16 (VEE), U3.18 (AX1), U3.19 (AX2), U3.20 (AY0), U3.21 (AY1), U3.40 (AY2), U3.42 (AX3), U3.43 (AX0), U4.1, U4.3 (GND); also elsewhere on the board
H_4080: J2.22, Q1.3 (D)
H_CAPLK: J2.24, Q2.3 (D)
H_COL0: J2.25, U3.2 (X15)
H_COL1: J2.12, U3.7 (X10)
H_COL2: J2.10, U3.8 (X11)
H_COL3: J2.8, U3.24 (X13)
H_COL4: J2.6, U3.25 (X12)
H_COL5: J2.4, U3.26 (X5)
H_COL6: J2.2, U3.27 (X4)
H_COL7: J2.14, U3.6 (X9)
H_COL8: J2.16, U3.5 (X8)
H_COL9: J2.18, U3.4 (X7)
H_COL10: J2.20, U3.3 (X6)
H_RESTORE: D3.1 (K), J2.5, Q3.3 (D); also elsewhere on the board
H_ROW0: J2.23, U3.11 (Y7)
H_ROW1: J2.21, U3.13 (Y6)
H_ROW2: J2.19, U3.15 (Y5)
H_ROW3: J2.9, U3.33 (Y0)
H_ROW4: J2.15, U3.39 (Y3)
H_ROW5: J2.13, U3.37 (Y2)
H_ROW6: J2.11, U3.35 (Y1)
H_ROW7: J2.17, U3.17 (Y4)
LED_DATA_5V: U4.4; also elsewhere on the board
LED_OUT: J3.2; also elsewhere on the board
MCU_4080_GATE: Q1.1 (G), R5.1, R6.2; also elsewhere on the board
MCU_CAPLK_GATE: Q2.1 (G), R7.1; also elsewhere on the board
MCU_LED_DATA: U4.2; also elsewhere on the board
MCU_RESTORE_GATE: Q3.1 (G), R12.1; also elsewhere on the board
MCU_RESTORE_SENSE: D3.2 (A); also elsewhere on the board
MCU_XP_CK: U3.34 (CS/CK); also elsewhere on the board
MCU_XP_DAT: U3.36 (DAT); also elsewhere on the board
MCU_XP_RST: R10.2, U3.41 (RST); also elsewhere on the board
MCU_XP_STB: R11.1, U3.14 (STB); also elsewhere on the board

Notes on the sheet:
Host side: CH446Q crosspoint mirrors the physical matrix onto the C128 ROW/COL lines. X = host columns, Y = host rows, in the order that routes cleanly from J2 (XP_X_OF_COL / XP_Y_OF_ROW in gen_sch.py); the firmware addresses through the same table. Serial address mode (P/S low): DAT, CS/CK, STB, R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
J2 pin n = ribbon conductor n. Odd pins -> D-sub 1..13, even pins -> D-sub 14..25. Fit an IDC box header, or solder the ribbon straight into the pads on a flat.
Lock lines
